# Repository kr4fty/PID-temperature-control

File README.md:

# PID-temperature-control

Temperature control of an oven/heater made with Arduino Uno (atmega328p microcontroller).
For it, a PID controller is used which will provide a constant temperature at the outlet, according to that established by the user.

This is an implementation of the ovenControl library for Arduino boards.

## Description:
The system maintains a constant temperature at which it is selected. It can vary between 0 and 420ºC.

## Software
These are the libraries required for their operation:

* Lcd: [Adafruit-PCD8544-Nokia-5110-LCD-library](https://github.com/adafruit/Adafruit-PCD8544-Nokia-5110-LCD-library).
* Keyboard: [AnalogKeypad](https://github.com/kr4fty/AnalogKeyPad).
* Menu: [MenuPCD8544](https://github.com/kr4fty/MenuPCD8544).
* K thermocouple: [K-Type_thermocouple-Library](https://github.com/kr4fty/K-Type_thermocouple-Library).
* OvenControl: [ovenControl](https://github.com/kr4fty/ovenControl).

## Hardware:
The system is composed of five main parts

* **The microcontroller**: brain in charge of the administration of resources.
* **Display and keyboard**: is the user interface. It uses a lcd of a Nokia 3310/5510 and a ladder type keyboard.
* **The temperature sensor**: in charge of constantly measuring the temperature of the oven/heater and in this way can make the feedback towards the control for the respective adjustments. For this function a K-type thermocouple  is used.
* **AC control**: in charge of handling AC, in this case I will use 220Vac/50Hz. For this purpose opto-thyristors are used, which act as a solid state relay.
* **Zero crossing detector**: in charge of activating the thyristors from the moment in which the alternating voltage wave is detected crosses by zero.For this function a K-type thermocouple is used.

## Video

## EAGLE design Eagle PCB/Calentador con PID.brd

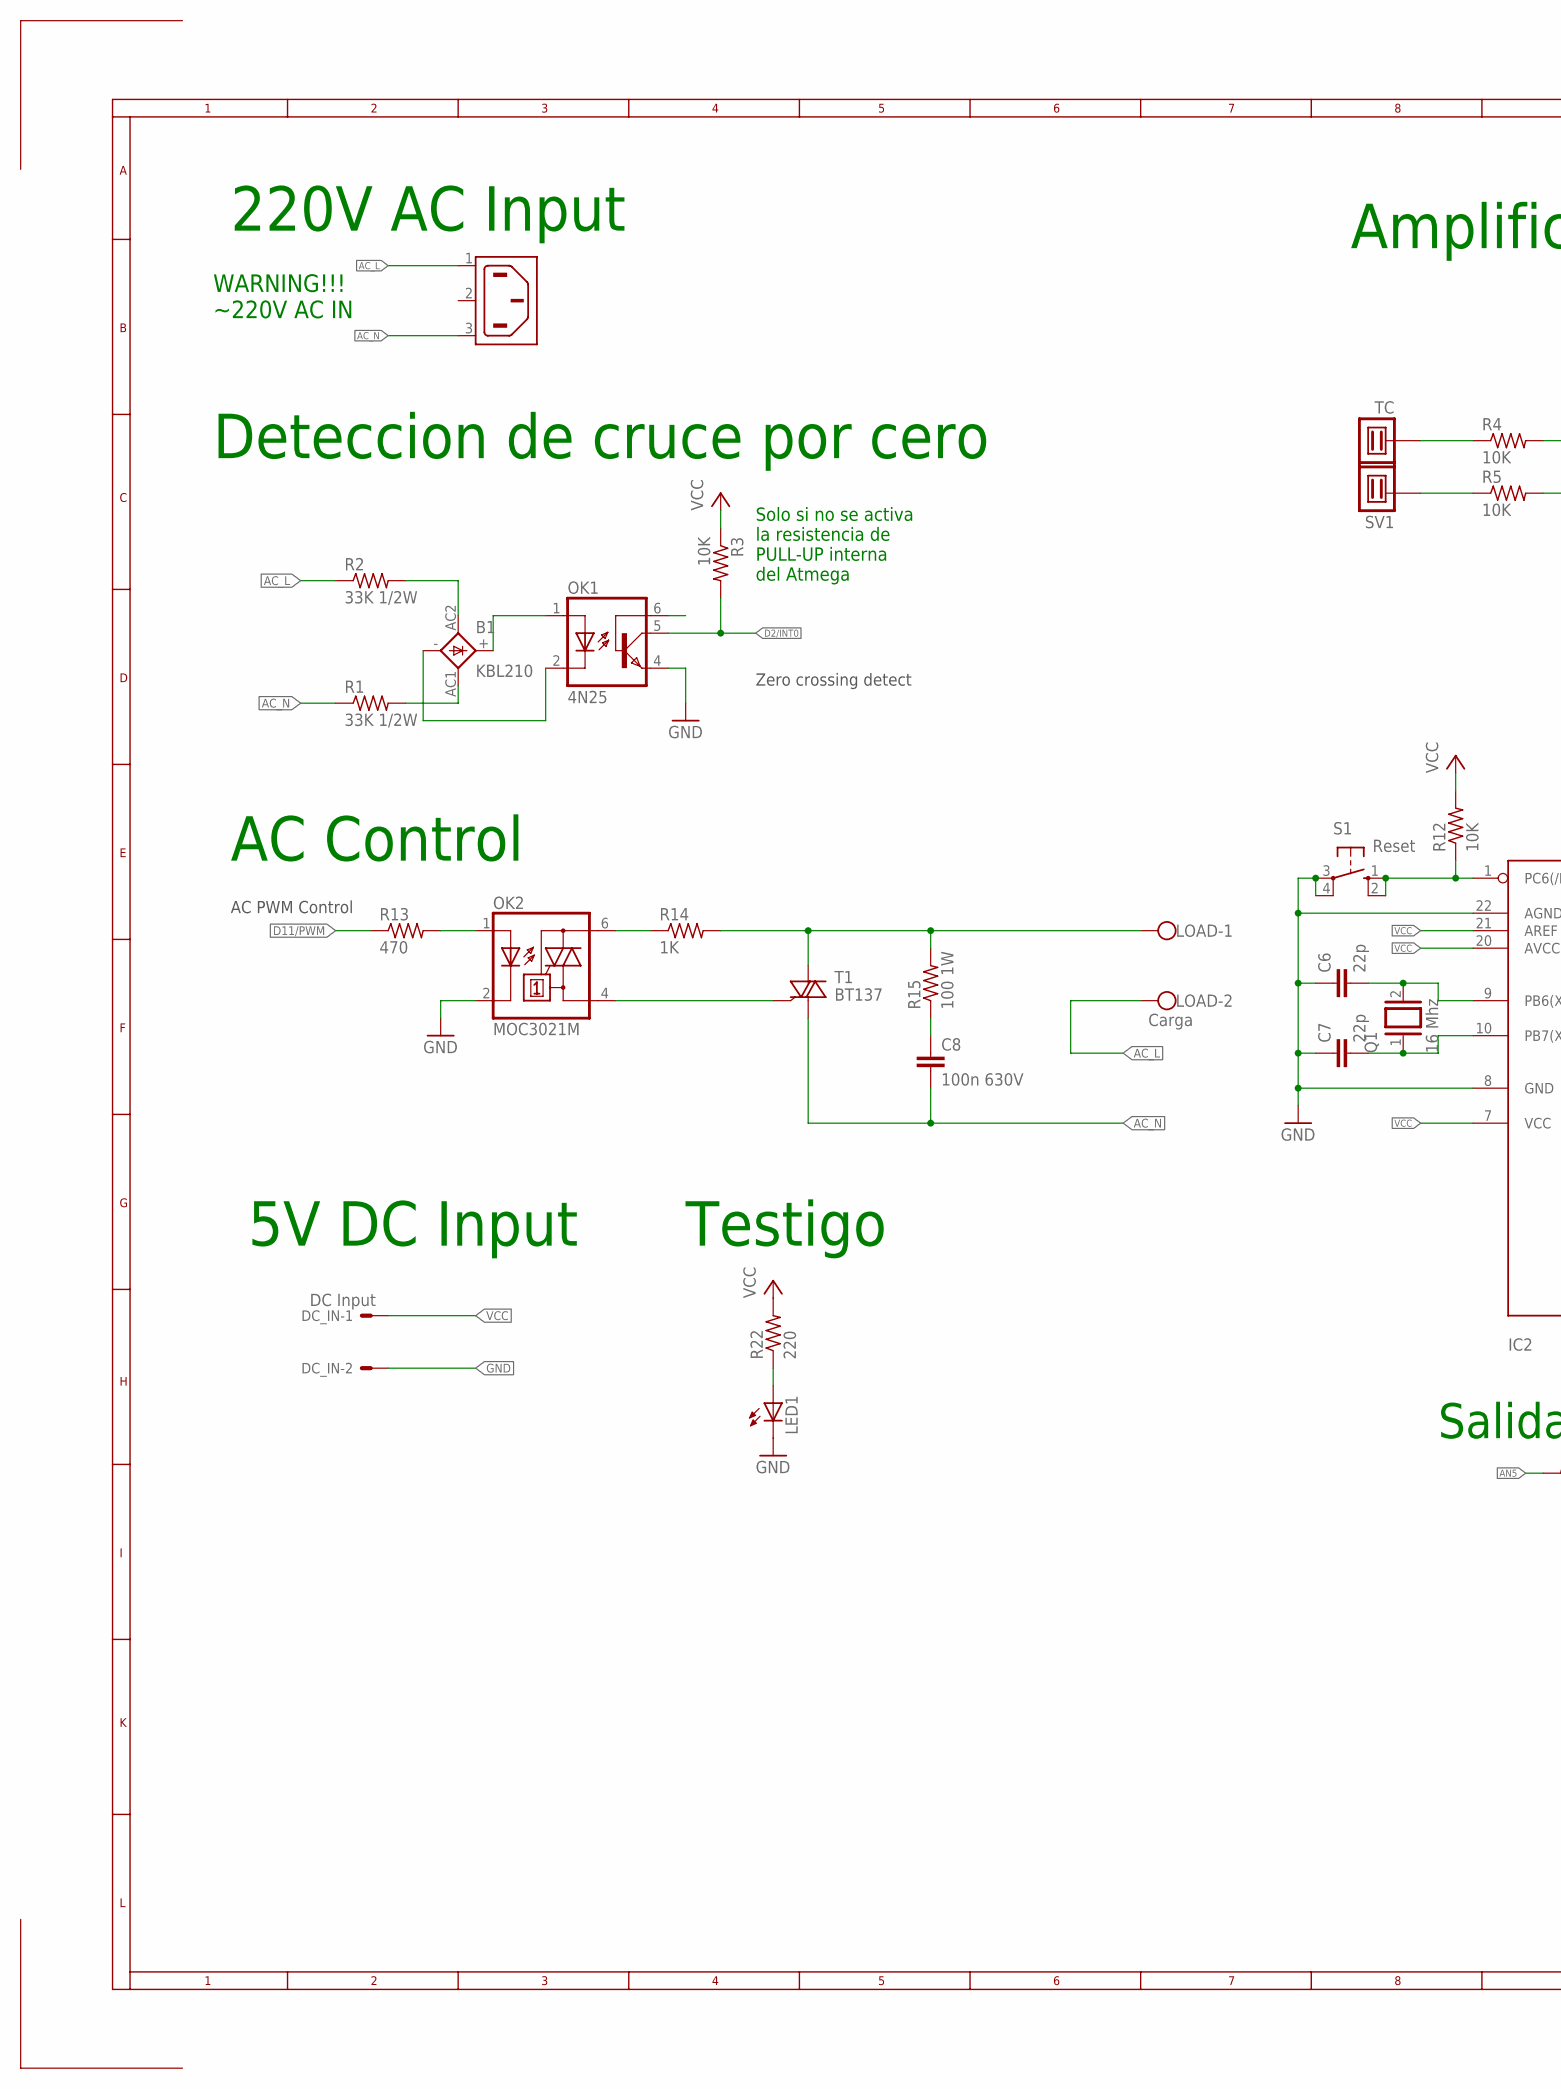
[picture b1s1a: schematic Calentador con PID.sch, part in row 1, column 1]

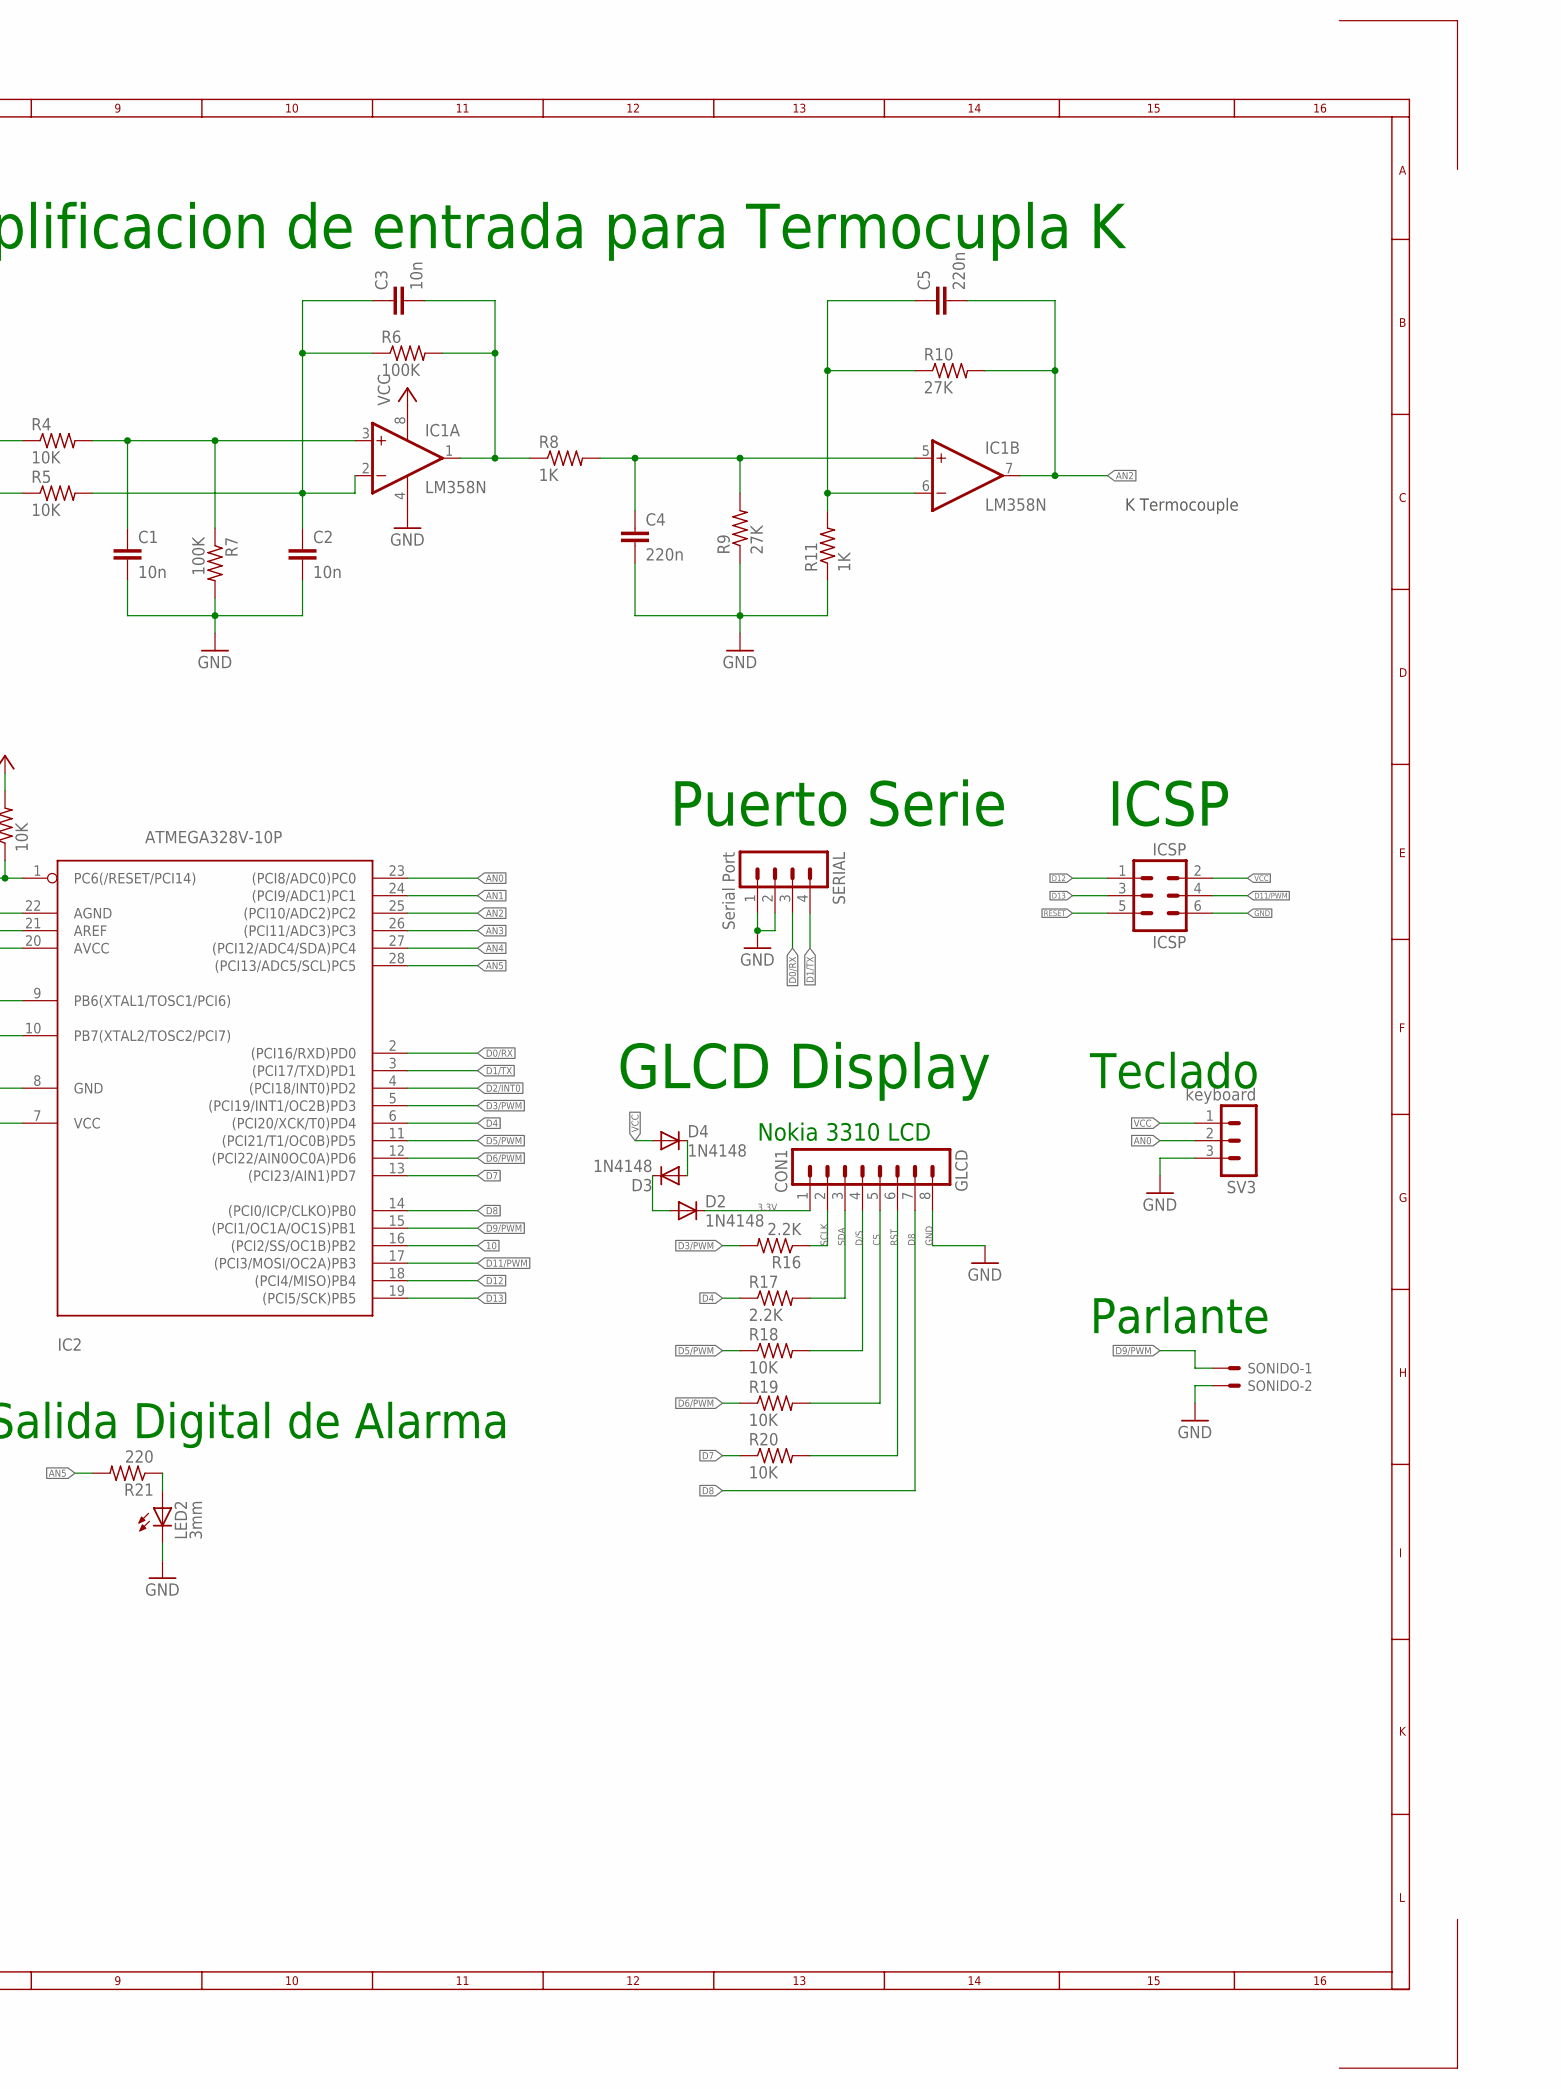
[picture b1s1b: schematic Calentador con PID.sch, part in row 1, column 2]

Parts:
B1: KBL210; KBL
C1, C2, C3: 10n; C050-024X044
C4, C5: 220n; C050-025X075
C6, C7: 22p; C050-025X075
C8: 100n 630V; C102-043X133
D2, D3, D4: 1N4148; DO35-7
DC_IN: DC Input; 22-23-2021
GLCD: CON1; MA08-1
IC1: LM358N; DIL08
IC2: ATMEGA328V-10P; DIL28-3
ICSP: ICSP; MA03-2
LED1: LED3MM
LED2: 3mm; Q62902-B155
LOAD: Carga; W237-102
OK1: 4N25; DIL06
OK2: MOC3021M; DIL06
Q1: 16 Mhz; QS
R1, R2: 33K 1/2W; 0207/2V
R3, R4, R5, R18, R19, R20: 10K; 0207/7
R6: 100K; 0207/2V
R7: 100K; 0207/7
R8, R14: 1K; 0207/2V
R9: 27K; 0207/7
R10: 27K; 0207/2V
R11: 1K; 0207/7
R12: 10K; 0207/15
R13: 470; 0207/10
R15: 100 1W; 0207/2V
R16, R17: 2.2K; 0207/10
R21: 220; 0207/7
R22: 220; 0207/2V
S1: Reset; B3F-10XX
SERIAL: Serial Port; MA04-1
SONIDO: 22-23-2021
SV1: TC; THERMOCOUPLE
SV3: keyboard; MA03-1
T1: BT137; TO220BV
X1: 6ESRM-P

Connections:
3.3V: D2.C, GLCD.1
10: IC2.16 ((PCI2/SS/OC1B)PB2)
AC_L: LOAD.2, R2.1, X1.1 (AC1)
AC_N: C8.2, R1.1, T1.T1 (A1), X1.3 (AC2)
AN0: IC2.23 ((PCI8/ADC0)PC0), SV3.2
AN1: IC2.24 ((PCI9/ADC1)PC1)
AN2: C5.2, IC1.7 (OUT), IC2.25 ((PCI10/ADC2)PC2), R10.2
AN3: IC2.26 ((PCI11/ADC3)PC3)
AN4: IC2.27 ((PCI12/ADC4/SDA)PC4)
AN5: IC2.28 ((PCI13/ADC5/SCL)PC5), R21.2
CS: GLCD.5, R19.2
D0/RX: IC2.2 ((PCI16/RXD)PD0), SERIAL.3
D1/TX: IC2.3 ((PCI17/TXD)PD1), SERIAL.4
D2/INT0: IC2.4 ((PCI18/INT0)PD2), OK1.5 (COL), R3.2
D3/PWM: IC2.5 ((PCI19/INT1/OC2B)PD3), R16.2
D4: IC2.6 ((PCI20/XCK/T0)PD4), R17.1
D5/PWM: IC2.11 ((PCI21/T1/OC0B)PD5), R18.1
D6/PWM: IC2.12 ((PCI22/AIN0OC0A)PD6), R19.1
D7: IC2.13 ((PCI23/AIN1)PD7), R20.1
D8: GLCD.7, IC2.14 ((PCI0/ICP/CLKO)PB0)
D9/PWM: IC2.15 ((PCI1/OC1A/OC1S)PB1), SONIDO.1
D11/PWM: IC2.17 ((PCI3/MOSI/OC2A)PB3), ICSP.4, R13.1
D12: IC2.18 ((PCI4/MISO)PB4), ICSP.1
D13: IC2.19 ((PCI5/SCK)PB5), ICSP.3
D/S: GLCD.4, R18.2
GND: C1.2, C2.2, C4.2, C6.1, C7.1, DC_IN.2, GLCD.8, IC1.4 (V-), IC2.8 (GND), IC2.22 (AGND), ICSP.6, LED1.K (C), LED2.K (C), OK1.4 (EMI), OK2.2 (C), R7.2, R9.1, R11.1, S1.3, S1.4 (P1), SERIAL.1, SERIAL.2, SONIDO.2, SV3.3
unnamed: OK2.1 (A), R13.2
unnamed: OK2.6 (A2), R14.1
unnamed: B1.AC2 (AC1), R2.2
unnamed: B1.AC1 (AC2), R1.2
unnamed: B1.+, OK1.1 (A)
unnamed: B1.-, OK1.2 (C)
unnamed: R4.1, SV1.2
unnamed: C4.1, IC1.5 (+IN), R8.2, R9.2
unnamed: R5.1, SV1.1
unnamed: C2.1, C3.1, IC1.2 (-IN), R5.2, R6.1
unnamed: C3.2, IC1.1 (OUT), R6.2, R8.1
unnamed: C5.1, IC1.6 (-IN), R10.1, R11.2
unnamed: C1.1, IC1.3 (+IN), R4.2, R7.1
unnamed: LOAD.1, R14.2, R15.2, T1.T2 (A2)
unnamed: OK2.4 (A1), T1.G
unnamed: C7.2, IC2.10 (PB7(XTAL2/TOSC2/PCI7)), Q1.1
unnamed: C6.2, IC2.9 (PB6(XTAL1/TOSC1/PCI6)), Q1.2
unnamed: D2.A, D3.C
unnamed: C8.1, R15.1
unnamed: D3.A, D4.C
unnamed: LED2.A, R21.1
unnamed: LED1.A, R22.1
RESET: IC2.1 (PC6(/RESET/PCI14)), ICSP.5, R12.1, S1.1 (S), S1.2 (S1)
RST: GLCD.6, R20.2
SCLK: GLCD.2, R16.1
SDA: GLCD.3, R17.2
VCC: D4.A, DC_IN.1, IC1.8 (V+), IC2.7 (VCC), IC2.20 (AVCC), IC2.21 (AREF), ICSP.2, R3.1, R12.2, R22.2, SV3.1

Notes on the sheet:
Solo si no se activa la resistencia de PULL-UP interna del Atmega
Deteccion de cruce por cero
Amplificacion de entrada para Termocupla K
Puerto Serie
ICSP
AC Control
WARNING!!! ~220V AC IN
220V AC Input
5V DC Input
GLCD Display
Nokia 3310 LCD
Teclado
Parlante
Salida Digital de Alarma
AC PWM Control
Zero crossing detect
K Termocouple
Testigo

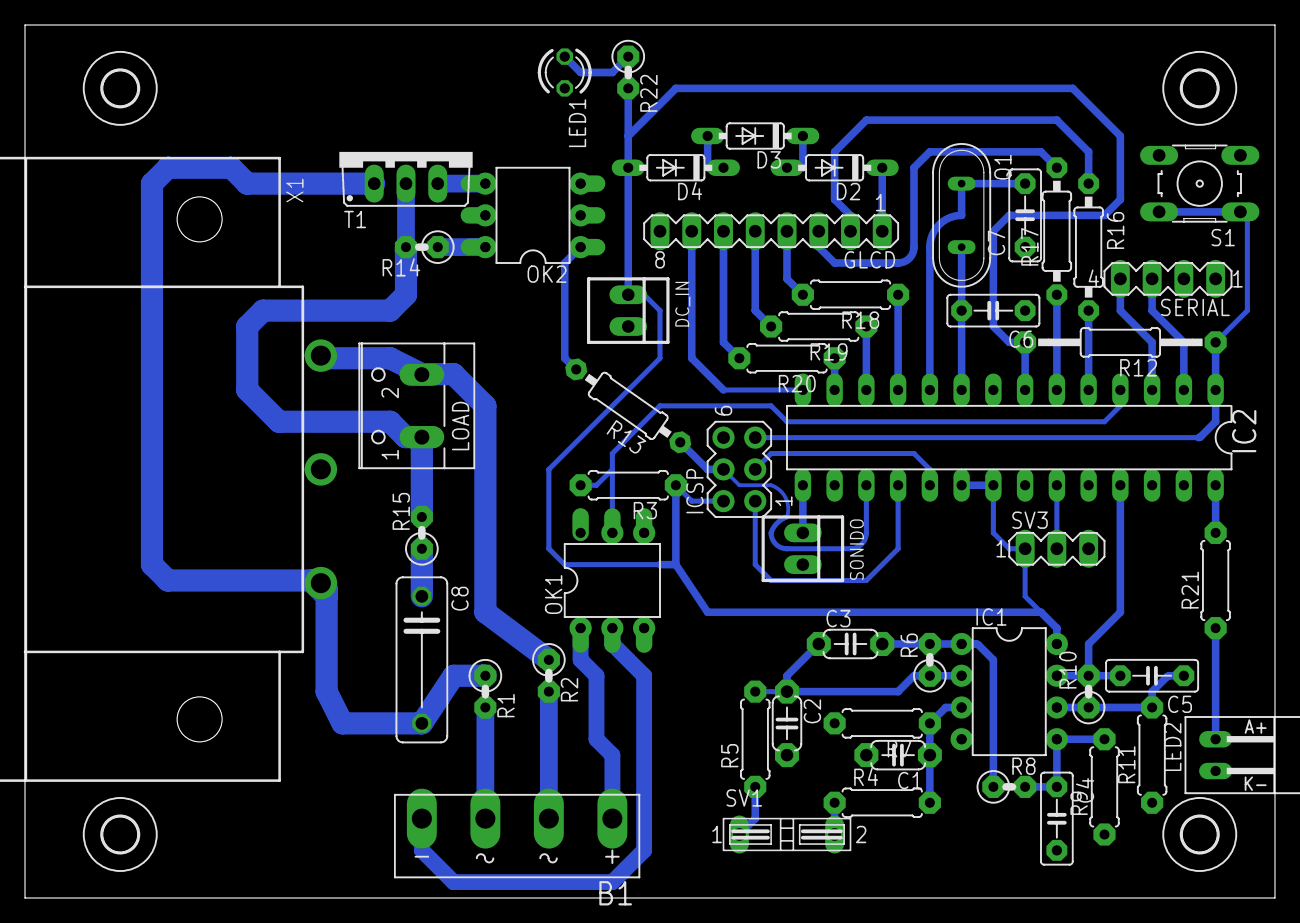
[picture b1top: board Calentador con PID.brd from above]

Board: 2 copper layers, 100.0 x 69.8 mm, 56 parts (0 on the bottom side), 49 nets.

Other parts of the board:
U$1, U$2, U$3, U$4: 2,8

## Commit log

2017-03-03 second commit
2017-03-05 Bug fixes. Block produced by acercade() function when process control was running
2017-03-05 prueba
2017-03-05 bugfix: avoid blocking the PID controller program
2017-03-06 Name change to variable: itsCancel to itsStop
2017-03-06 probando actualizar repo utilizando git+ de Atom/PlatmormIO
2017-03-22 Add video in README.md
2017-06-01 rename folder
2017-06-01 license GPLv2
2022-12-28 wrong translation
